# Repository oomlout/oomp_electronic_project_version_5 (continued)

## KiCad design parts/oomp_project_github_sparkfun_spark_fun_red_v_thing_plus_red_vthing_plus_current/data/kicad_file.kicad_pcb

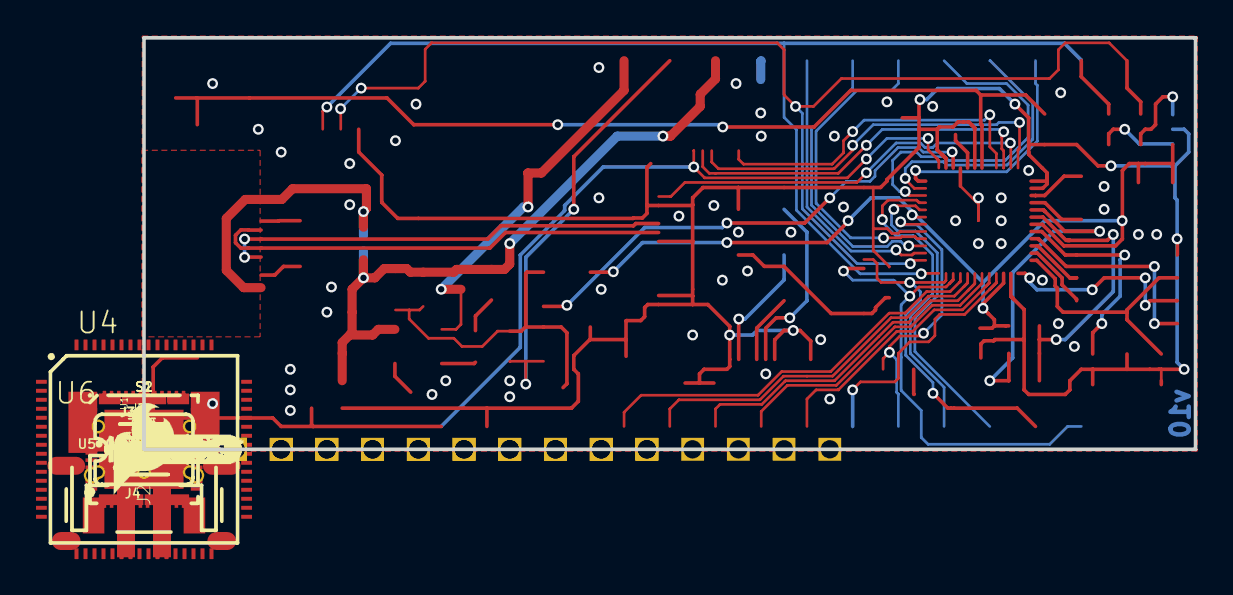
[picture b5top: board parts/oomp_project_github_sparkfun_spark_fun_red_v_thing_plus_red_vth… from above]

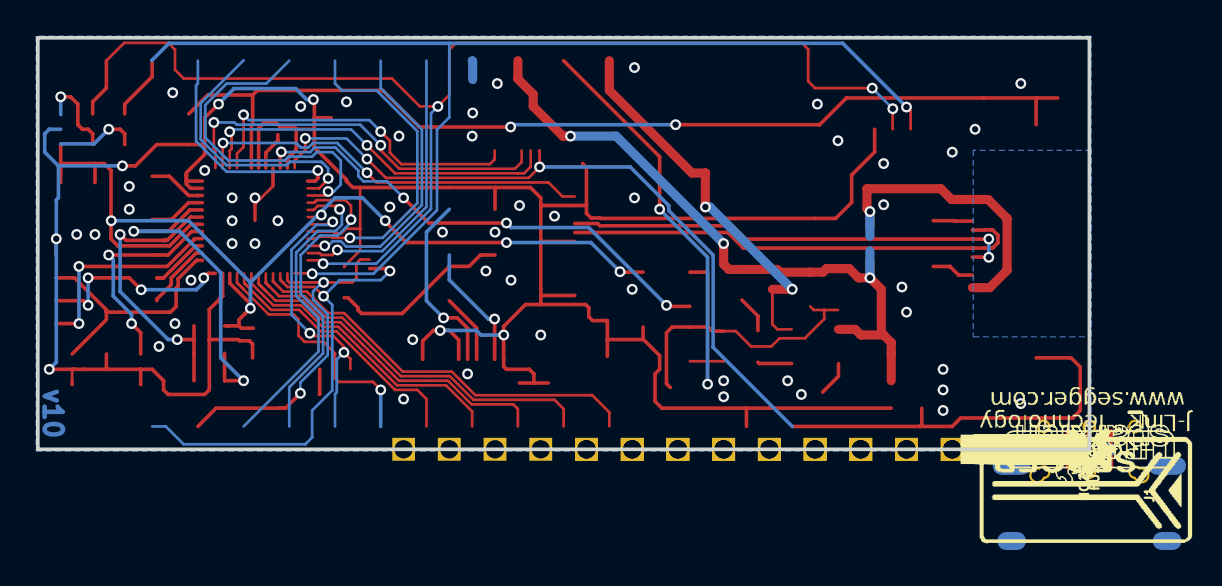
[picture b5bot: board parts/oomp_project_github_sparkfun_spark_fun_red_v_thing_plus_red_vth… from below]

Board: 2 copper layers, 58.4 x 22.9 mm, 137 parts (40 on the bottom side), 60 nets.

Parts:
C1, C3, C30: 10uF; 0603
C2, C10, C12, C17, C18, C23, C24, C25, C26, C27, C28, C29: 0.1uF; 0603
C4, C9, C16: 1.0uF; 0603
C5: 4.7uF; 0603
C6: 47uF/6.3V; 0805
C7: 470nF; 0603
C15: 10uF; EIA3216
D1: 1A/23V/620mV; SOD-323
D2, D4: 24V; 0603
D3: Yellow; LED-0603
F1: 6V 0.5A; 0805
FRAME1, FRAME2: FRAME-LETTER; CREATIVE_COMMONS
FUSE0: JUMPER-SMT_2_NO_NO-SILK; SMT-JUMPER_2_NO_NO-SILK
I2C0: JUMPER-SMT_3_NO_NO-SILK; SMT-JUMPER_3_NO_NO-SILK
J1: FEMALE 2x3; 2X3_TEST_POINTS
J2: USB Female Type C Connector; USB-C-16P
J3: JST-2-SMD
J4: QWIIC_RIGHT_ANGLE; JST04_1MM_RA
J6: 1X12_SM_SQ_NOSILK
J7: 1X16_SM_SQ_NOSILK
JP8, JP9, JP15, JP16: FIDUCIAL1X2; FIDUCIAL-1X2
LED1: BLUE; LED-0603
LOGO2: SFE_LOGO_FLAME.2_INCH; SFE_LOGO_FLAME_.2
NC/GND0: JUMPER-SMT_2_NO_NO-SILK; SMT-JUMPER_2_NO_NO-SILK
Q1: 3.1A/30V/105mΩ; SOT23-3
R1, R9, R10: 4.7k; 0603
R3, R4, R5, R6, R7, R20: 100k; 0603
R8: 100; 0603
R11: 10k; 0603
R12: 2.0k; 0603
R13: 1k; 0603
R18, R19: 5.1k; 0603
S1, S2: MOMENTARY-SWITCH-SPST-SMD-4.6X2.8MM; TACTILE_SWITCH_SMD_4.6X2.8MM
U1: MCP73831; SOT23-5
U2: AP2127K-1.8V; SOT23-5
U3: AP2112-3.3V; SOT23-5
U4: MK22FN128VLH10; LQFP-64
U5: 32MBit; SO08
U6: FE310; QFN-48-.4MMPITCH
U$1: (QWIIC)
U$2: 96
U$3: 26
U$4: 15
U$5: 04
U$6: SDA9
U$8: TXO1
U$9: 107
U$11: 118
U$12: 1811
U$13: RED#V_THING_PLUS_BOARD_SILK#02#JPG
U$14: 1912
U$15: 2013
U$16: OSHW-LOGOS; OSHW-LOGO-S
U$17: 2114
U$18: 2215
U$19: 2316
U$20: EN18
U$21, U$28: GND0
U$22, U$27: NC17
U$23: RXI2
U$24: SCK5
U$25: SCL10
U$26: VBAT19
U$29: #RESET34
U$30: 3V332
U$31: 3V333
U$32: 015
U$33: 114
U$34: 213
U$35: 912
U$36: 1011
U$37: 1110
U$38: CHG0
U$39: 1828
U$40: 1927
U$41: 2026
U$42: RED#V_THING_PLUS_BOARD_SILK#01#JPG
U$43: 2125
U$44: 2224
U$45: SEGGERLOGO#PNG
U$46: 50
U$47: 2323
U$48: EN8
U$49: ASDFKJGHB#JPG
U$50: I2C_______0
U$51, U$67: GND29
U$52: MISO#421
U$53: MOSI#320
U$54: NC#GND31
U$55: NC30
U$56: RST2
U$57: RXI#1619
U$58: SCK#522
U$59: SCL#1316
U$60: SDA#1217
U$61: SI0
U$62: SO1
U$63: TXO#1718
U$64: VBAT7
U$65: VUSB3
U$66: VUSB9
U$68: RESET1
U$69: WAKE0
Y1: 32.768KHZ; CRYSTAL-SMD-2X1.2MM
Y2: 16MHz; RESONATOR-SMD-3.2X1.3

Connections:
1.8V: C1.1, C9.1, C23.1, C24.1, R8.1, U2.5, U6.6, U6.30, U6.46
3.3V: C2.1, C3.1, C6.1, C7.1, C16.1, C17.1, C18.1, C27.1, C28.1, C29.1, C30.1, I2C0.2, J1.2, J4.2, J7.15, R3.2, R5.2, R6.2, R7.2, R20.2, U3.5, U4.3, U4.7, U4.13, U4.14, U4.21, U4.26, U4.30, U4.48, U5.8, U6.11, U6.12, U6.19, U6.23, U6.32, U6.47, Y1.4
5V: C4.1, D1.C, Q1.2, R4.1, U2.1, U3.1
CORE_ENABLE: U2.3, U6.22
D+: J2.A6, J2.B6, U4.5
D-: J2.A7, J2.B7, U4.6
DBG_RESET: J1.4, R20.1, U4.34
DBG_SWDCLK: J1.3, U4.22
DBG_SWDIO: J1.1, U4.25
DBG_SWO: J1.5, U4.24
EN: J6.11, R4.2, U3.3
GND: C1.2, C2.2, C3.2, C4.2, C5.2, C6.2, C7.2, C9.2, C10.2, C12.2, C15.-, C16.2, C17.2, C18.2, C23.2, C24.2, C27.2, C28.2, C29.2, C30.2, D2.1, D4.1, J1.6, J2.GND, J2.GND2, J3.1, J4.1, J7.1, J7.13, LED1.C, NC/GND0.1, R11.1, R12.1, R18.1, R19.1, S1.3, S1.4, S2.3, S2.4, U1.2, U2.2, U3.2, U4.4, U4.15, U4.16, U4.31, U4.47, U5.4, U6.21, U6.49, Y1.2, Y2.2
IO0: J6.3, U6.25
IO1: J6.4, U6.26
IO2: J6.5, U6.27
IO9: J6.6, U6.33
IO10: J6.7, U6.34
IO11: J6.8, U6.35
IO18: J7.12, U6.40
IO19: J7.11, U6.41
IO20: J7.10, U6.42
IO21: J7.9, U6.43
IO22: J7.8, U6.44
IO23: J7.7, U6.45
unnamed: LED1.A, R1.2
unnamed: U6.10, Y2.1
unnamed: J6.9, NC/GND0.2
unnamed: I2C0.1, R9.2
unnamed: I2C0.3, R10.2
unnamed: U6.9, Y2.3
unnamed: U6.20, Y1.3
unnamed: R12.2, U1.5
unnamed: C25.2, C26.2, U6.8
unnamed: D3.C, U1.1
unnamed: J2.B5, R18.2
unnamed: D3.A, R13.2
unnamed: J2.A5, R19.2
PLL_AVDD: C25.1, C26.1, R8.2, U6.7
QSPI_0: U5.5, U6.4
QSPI_1: U5.2, U6.3
QSPI_2: U5.3, U6.2
QSPI_3: R5.1, U5.7, U6.1
QSPI_CS: R3.1, U5.1, U6.5
QSPI_SCK: U5.6, U6.48
RXI: J7.3, U4.40, U6.38
SCL: J4.4, J6.2, R9.1, U6.37
SDA: J4.3, J6.1, R10.1, U6.36
SPI_MISO: J7.4, U6.29
SPI_MOSI: J7.5, U6.28
SPI_SCK: J7.6, R1.1, U6.31
TCK: U4.62, U6.13
TDI: U4.59, U6.16
TDO: U4.2, U6.14
TMS: U4.63, U6.15
TXO: J7.2, U4.39, U6.39
VUSB: C10.1, F1.1, FUSE0.1, J2.VBUS1, J2.VBUS2
V_BATT: J3.2, J6.12, Q1.3, U1.3
V_USB: C5.1, C12.1, C15.+, D1.A, F1.2, FUSE0.2, J6.10, Q1.1, R11.2, R13.1, U1.4
~RESET: D4.2, J7.16, R6.1, S2.1, S2.2, U4.64, U6.24
~WAKE: D2.2, R7.1, S1.1, S1.2, U6.18

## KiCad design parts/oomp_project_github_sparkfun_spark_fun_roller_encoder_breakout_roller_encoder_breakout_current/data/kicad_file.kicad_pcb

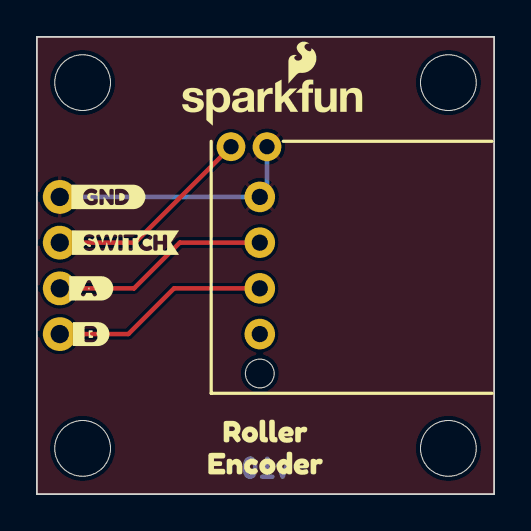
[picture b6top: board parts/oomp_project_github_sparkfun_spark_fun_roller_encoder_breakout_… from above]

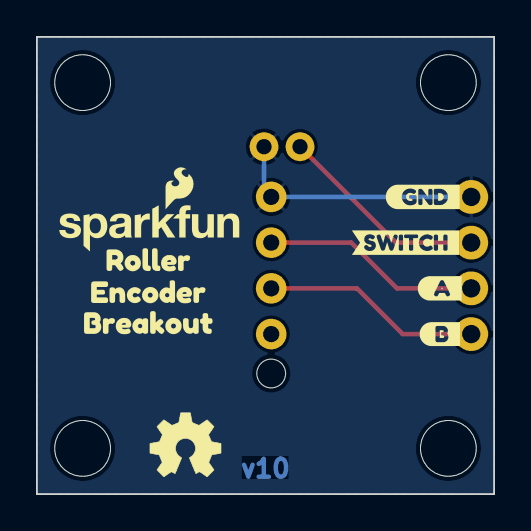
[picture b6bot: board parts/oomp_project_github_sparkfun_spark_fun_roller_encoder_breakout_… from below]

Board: 2 copper layers, 25.4 x 25.4 mm, 21 parts (8 on the bottom side), 4 nets.

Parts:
G1: OSHW_Logo; Creative_Commons_License
J1: Conn_01x04; 1x04
Ref**: Val**; OSHW_Logo_4mm
ST1, ST2, ST3, ST4: Standoff
SW1: Roller_Encoder_Switch; RollerEncoder
kibuzzard-67946CBF: G***; kibuzzard-67946CBF
kibuzzard-67946CF5: G***; kibuzzard-67946CF5
kibuzzard-67946D1E: G***; kibuzzard-67946D1E
kibuzzard-67946D7C: G***; kibuzzard-67946D7C
kibuzzard-67946D9A: G***; kibuzzard-67946D9A
kibuzzard-67946D71: G***; kibuzzard-67946D71
kibuzzard-67946DB3: G***; kibuzzard-67946DB3
kibuzzard-679465CE, kibuzzard-679465CE#2: G***; kibuzzard-679465CE
kibuzzard-679465D4, kibuzzard-679465D4#2: G***; kibuzzard-679465D4
kibuzzard-6794660B: G***; kibuzzard-6794660B
kibuzzard-6794662B: G***; kibuzzard-6794662B

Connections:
A: J1.2, SW1.A
B: J1.1, SW1.B
GND: J1.4, SW1.C, SW1.S2
SWITCH: J1.3, SW1.S1

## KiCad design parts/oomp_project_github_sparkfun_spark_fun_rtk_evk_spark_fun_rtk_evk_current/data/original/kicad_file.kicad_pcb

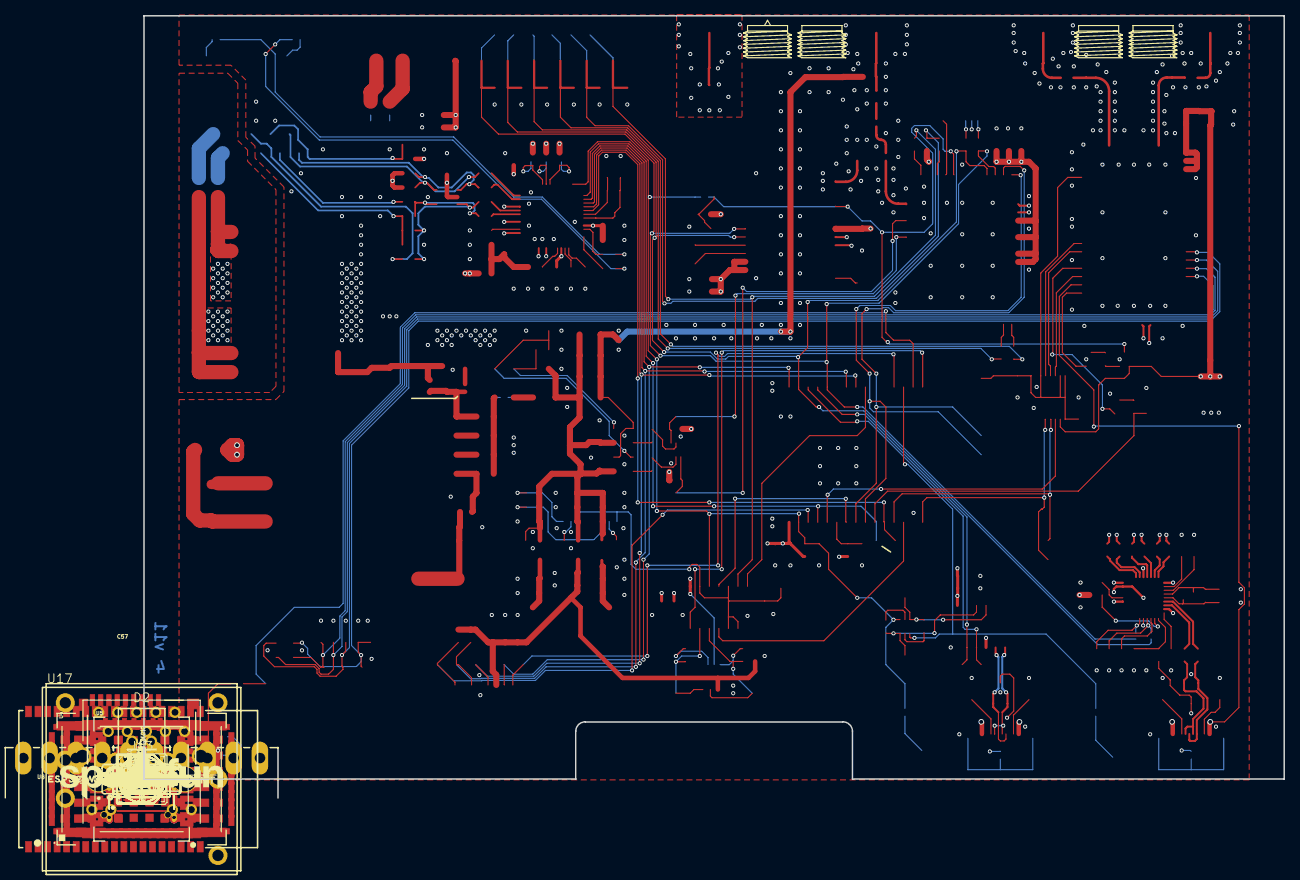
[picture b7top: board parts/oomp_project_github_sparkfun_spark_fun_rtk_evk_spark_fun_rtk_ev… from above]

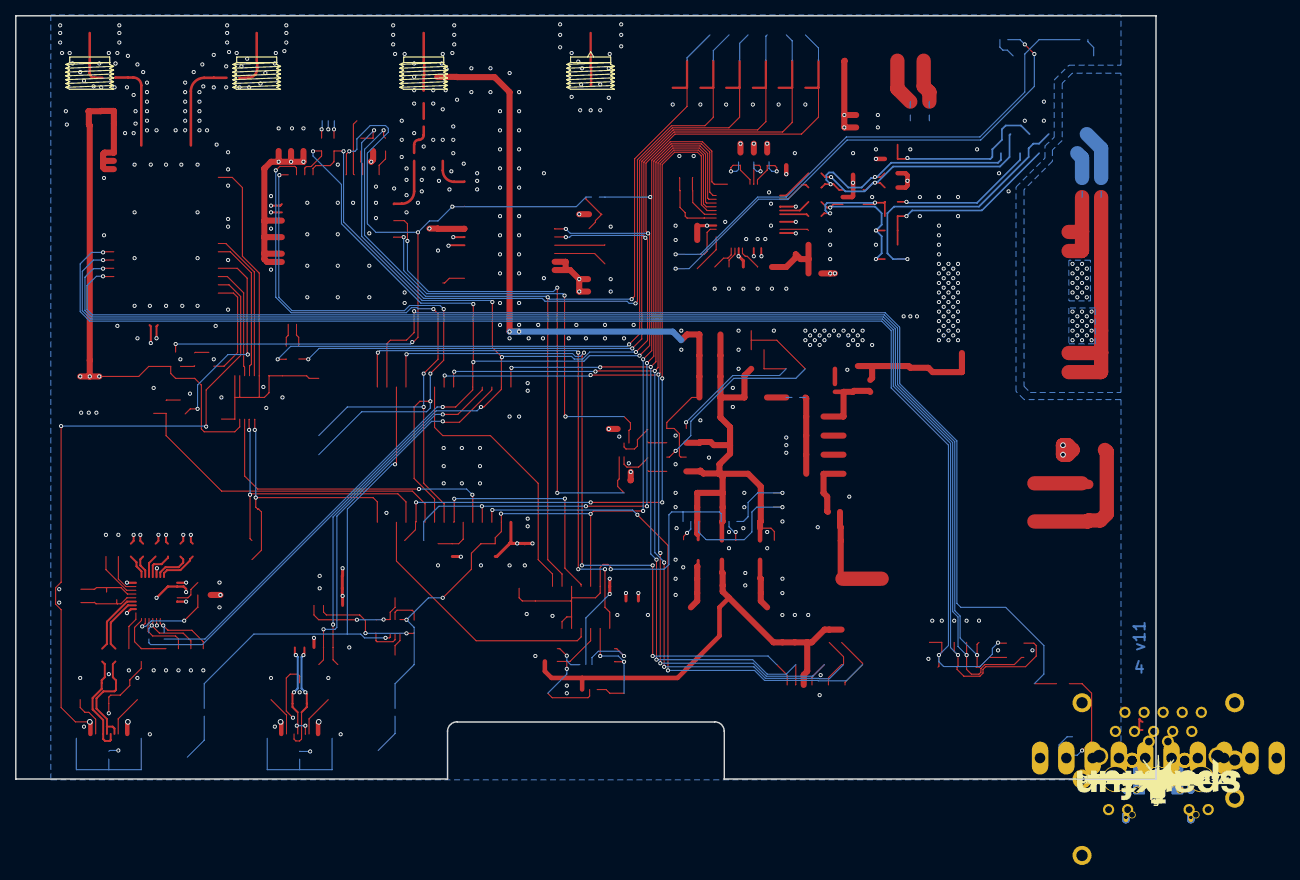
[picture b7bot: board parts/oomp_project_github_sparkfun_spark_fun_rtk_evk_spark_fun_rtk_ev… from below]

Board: 4 copper layers, 151.8 x 101.6 mm, 435 parts (97 on the bottom side), 176 nets.

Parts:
!SAFEBOOT_NEO!0: TEST-POINTPOGO_PTH; 1X01_NO_SILK
!SAFEBOOT_ZED!0: TEST-POINTPOGO_PTH; 1X01_NO_SILK
ACT0: JUMPER-SMT_2_NC_TRACE_SILK; SMT-JUMPER_2_NC_TRACE_SILK
ANT_DET0: TEST-POINTPOGO_PTH; 1X01_NO_SILK
ANT_SHT0: TEST-POINTPOGO_PTH; 1X01_NO_SILK
BOOT0: MOMENTARY-SWITCH-SPST-PTH-RIGHT-ANGLE-8-020; TACTILE_SWITCH_PTH_RA_8-020
BOOT_SW0: JUMPER-SMT_2_NC_TRACE_SILK; SMT-JUMPER_2_NC_TRACE_SILK
BYPASS1, BYPASS2: NO PASTE; SMT-JUMPER_2_SOIC-PAD_NO-PASTE
C1, C3, C5, C6, C8, C9, C10, C14, C18, C22, C23, C25, C26, C29, C56, C59, C60: 2.2uF; 0603
C2, C7, C15, C17, C19, C21, C30, C31, C33, C34, C35, C36, C37, C38, C52, C53, C54, C58, C61, C62, C65, C66, C67, C68, C69, C70, C75, C78: 0.1uF; 0603
C4, C40, C43: 10nF; 0603
C11, C13, C71, C72, C73, C74: 47pF; 0603
C12, C24: 1.0uF; 0603
C16, C48, C57, C76: 100uF; PANASONIC_D
C20, C32, C39, C55: 10uF; 0603
C27, C28: 10pF; 0603
C41: 4.7uF; 0603
C42: 1nF; 1206
C44, C45: 6.8nF; 0603
C46: 22nF; 0603
C47, C49, C50, C51, C77, C84, C85: 10uF; 0805
C63, C64: 18pF; 0603
C79: 15pF; 0603
C80: 8.2pF; 0603
C81: 68pF; 0603
C82, C83: 33pF; 0603
C86: 47UF; PANASONIC_D
D1, D12, D13, D15, D16, D17, D18, D19, D20: PESD0402-0402; 0402
D2: LED-RIGHT-ANGLE-PTH-GREEN; CBI-RIGHT-ANGLE-PTH
D3: PESD0402; 0402
D4, D5, D6, D9: 3A/10V/280mV; SOD-323
D7, D8, D10: ESD Diode; SOT-23-6
D11: TVS_DIODE; SOT23-6L
D14: 3A/40V; SMA-DIODE
DET0: TEST-POINTPOGO_PTH; 1X01_NO_SILK
DTR0: TEST-POINTPOGO_PTH; 1X01_NO_SILK
ESP32_RF0: ANTENNA-SMA-GROUNDEDEDGE_RPSMA; RP-SMA-EDGE
ETH_CS0: TEST-POINTPOGO_PTH; 1X01_NO_SILK
ETH_INT0: TEST-POINTPOGO_PTH; 1X01_NO_SILK
F1: 6V/2A; 1210
FB1: 600Ω; 0805
FB2: 470Ω; 0603
FD1, FD2, FD3, FD4: FIDUCIAL1X2; FIDUCIAL-1X2
FRAME1: FRAME-LEDGER; CREATIVE_COMMONS
FRAME2: FRAME-LEDGERNO_FOOTPRINT; DUMMY
GND0: TEST-POINTPOGO_PTH; 1X01_NO_SILK
GNSS_RESET0: JUMPER-COMBO_2_NO; COMBO-JUMPER_2_NO
GNSS_RF0: ANTENNA-SMA-GROUNDEDEDGE_SMA; SMA-EDGE
H1, H2, H3, H4, H5, H6: STAND-OFFTIGHT; STAND-OFF-TIGHT
I2C0, I2C1: JUMPER-SMT_3_NO_SILK; SMT-JUMPER_3_NO_SILK
J1, J6: USB-C-16P_4LAYER-PADS
J2: NANO_SIM_PP
J3: MICRO-SD-PUSH-PUSH-EXT-PIN; MICROSD-EXTERNALPIN
J4: Vertical Qwiic Connector; JST04_1MM_VERT
J8: U.FL_REDUCED_FOOTPRINT
J9: MAGJACK-POE; MAGJACK-SYM_LED
J13: 1X10_SCREW_TERMINAL_3.5MM
L1, L4: 2.2uH; 0805-WIDE
L2, L3: DNP; 0603_NO-CREAM
LARA_RF1, LARA_RF2: ANTENNA-SMA-GROUNDEDEDGE_SMA; SMA-EDGE
LED0: JUMPER-SMT_2_NC_TRACE_SILK; SMT-JUMPER_2_NC_TRACE_SILK
LINK0: JUMPER-SMT_2_NC_TRACE_SILK; SMT-JUMPER_2_NC_TRACE_SILK
LOAD0: JUMPER-SMT_2_NC_TRACE_SILK; SMT-JUMPER_2_NC_TRACE_SILK
LOGO1: SPECIAL_INSTRUCTIONS-ORDERING; ORDERING_INSTRUCTIONS
LOGO2: QWIIC_LOGO_6MM; QWIIC_6MM
LOGO4: OSHW-LOGOS; OSHW-LOGO-S
LOGO5, LOGO7: SFE_LOGO_NAME.2_INCH; SFE_LOGO_NAME_.2
LOGO6, LOGO8: SFE_LOGO_FLAME.2_INCH; SFE_LOGO_FLAME_.2
MEAS0: JUMPER-COMBO_2_NC_TRACE; COMBO-JUMPER_2_NC_TRACE
NEO_RX0: TEST-POINTPOGO_PTH; 1X01_NO_SILK
NEO_TX0: TEST-POINTPOGO_PTH; 1X01_NO_SILK
PICO0: TEST-POINTPOGO_PTH; 1X01_NO_SILK
PM0, PM1, PM2: JUMPER-SMT_2_NO_SILK; SMT-JUMPER_2_NO_SILK
POCI0: TEST-POINTPOGO_PTH; 1X01_NO_SILK
PW+0: JUMPER-COMBO_2_NC_TRACE; COMBO-JUMPER_2_NC_TRACE
PW-0: JUMPER-COMBO_2_NC_TRACE; COMBO-JUMPER_2_NC_TRACE
PWREN0: TEST-POINTPOGO_PTH; 1X01_NO_SILK
Q1, Q2: SC70-6
Q5, Q6: 310mA/60V/1.6Ω; SOT323
R1, R2, R33, R34: 5.1k; 0603
R3, R4, R5, R11, R15, R28, R30, R31, R32, R49, R54, R57, R58, R64: 10k; 0603
R6, R27, R36, R37, R38, R39, R46, R47: 33; 0603
R7, R8, R9, R10, R22, R23, R66, R67: 27; 0603
R12: 12k; 0603
R13, R24: 1M; 0603
R14, R17, R18, R20, R21, R44, R48, R50, R51, R52, R65, R69: 100k; 0603
R16, R19, R71, R72: 2.2k; 0603
R25, R26, R53, R56, R63, R68, R70: 1k; 0603
R29: 12.4k; 0603
R35, R40, R41, R42: 49.9; 0603
R43: 10; 0603
R45, R55, R59, R60, R61: 49.9 1/2W; 1206
R62: 470; 0603
RESET0: MOMENTARY-SWITCH-SPST-PTH-RIGHT-ANGLE-8-020; TACTILE_SWITCH_PTH_RA_8-020
RESET_SW0: JUMPER-SMT_2_NC_TRACE_SILK; SMT-JUMPER_2_NC_TRACE_SILK
RTS0: TEST-POINTPOGO_PTH; 1X01_NO_SILK
RX0, RX2: TEST-POINTPOGO_PTH; 1X01_NO_SILK
RXD0: TEST-POINTPOGO_PTH; 1X01_NO_SILK
SCK0: TEST-POINTPOGO_PTH; 1X01_NO_SILK
SCL0, SCL2: TEST-POINTPOGO_PTH; 1X01_NO_SILK
SDA0, SDA2: TEST-POINTPOGO_PTH; 1X01_NO_SILK
SD_CS0: TEST-POINTPOGO_PTH; 1X01_NO_SILK
SHLD1, SHLD2: JUMPER-SMT_2_NC_TRACE_SILK; SMT-JUMPER_2_NC_TRACE_SILK
SPWR0: JUMPER-SMT_3_1-NC_TRACE_SILK; SMT-JUMPER_3_1-NC_TRACE_SILK
TP0: TEST-POINTPOGO_PTH; 1X01_NO_SILK
TPWR0: JUMPER-SMT_3_1-NC_TRACE_SILK; SMT-JUMPER_3_1-NC_TRACE_SILK
TP_BOOT0: TEST-POINTPOGO_PTH; 1X01_NO_SILK
TP_LED0: TEST-POINTPOGO_PTH; 1X01_NO_SILK
TX0, TX2: TEST-POINTPOGO_PTH; 1X01_NO_SILK
TXD0: TEST-POINTPOGO_PTH; 1X01_NO_SILK
U1: ESP32-WROVER-IE; ESP32-WROVER-E_IE
U2: CH340C; SO016
U3, U6: XC6222B331MR-G; SOT23-5
U4: U-BLOX_ZED-F9P; ZED-F9P
U5: U-BLOX_NEO-D9S-00B; NEO-M9N_M8T_M8U_D9S
U7: W5500; LQFP-48
U8: LARA-R6001D; LARA-LGA
U9: 74LVC4066D_QUAD_BILATERAL_SWITCH; SO14
U10: POE_PSU-DP990X; DP990X
U11, U13: MCP6021T; SOT23-5
U12: AP7361C-33; UDFN-8
U14: BP2G1+_POWER_SPLITTER; XX21
U15: USB251XB_USB2514B; QFN-36
U16: SN74AVC4T774PW; SOP65P640X120-16N
U17: URB2405YMD; URB_YMD-15WR3
U18: 74HC1G04; SOT353
U$2: 33_#_ZED_RXI0
U$3, U$45: #SHLD#0
U$4, U$46, U$48: #I�C#0
U$5, U$113: PW#0
U$6, U$114: PW#1
U$7, U$149: 0_#_BOOT0
U$8, U$12, U$41, U$93: #SAFEBOOT#2226
U$9: #ACT#0
U$10: #LINK#1
U$11, U$13: RTK_EVK0
U$14: NEO_TX2
U$15: NEO_RX3
U$16, U$18: GND2
U$17, U$65: 3V3_SW20
U$19: 12_#_SDA20
U$20: 15_#_SCL213
U$21: ESP32_WIFI_#_BT0
U$22, U$23: 3V3_SW3
U$24, U$107: VCCA0
U$25, U$26: 21_#_SDA4
U$28, U$30: 22_#_SCL22
U$29, U$111: 27_#_#ETH_CS#0
U$31, U$32: ZED_RX223
U$33, U$36: ZED_TX2224
U$34, U$99: 1_#_TX20
U$35, U$100: 3_#_RX20
U$37, U$38: ZED_EXTINT2225
U$39, U$40: ZED_TP2226
U$42, U$94: ANT_DET2227
U$43, U$95: #ANT_SHT#2228
U$44, U$106: 9#2230
U$47, U$104: 99#2230
U$49, U$105: V_ANT2229
U$55, U$76: RTS2231
U$56, U$77: DTR2232
U$57, U$66: 2_#_LED0
U$58: #LED#2234
U$59, U$88: 3V3_SW25
U$60, U$87: 3V325
U$61, U$86: 5V25
U$62, U$84: MEAS2
U$63, U$70: VIN#0
U$64: 36_#_SD_DET0
U$67: #PMODE0#0
U$68: #PMODE1#1
U$69: #PMODE2#2
U$71, U$72: VIN#1
U$73, U$108: 14_#_RXDO0
U$74: #RESET#0
U$75, U$103: 13_#_TXDI15
U$78: ESP320
U$79, U$110: 39_#_#ETH_INT#0
U$80, U$141: PWR_EN2233
U$81: V_POE0
U$82: V_USB3
U$83: V_USB24
U$85: VIN1
U$89: 4_#_#SD_CS#15
U$90: 25_#_ZED_TXO0
U$91, U$92: NO0
U$96: CELLULAR2
U$97: L#BAND1
U$98: 23_#_PICO23
U$101: 19_#_POCI19
U$102: 18_#_SCK6
U$115, U$116: VCCIO0
U$117: #3V3_SW_EN#0
U$118: #3V3_SW2_EN#0
U$135, U$143: GND12
U$136: POE_LOAD0
U$146, U$147: HIGH_TEMP_WARNING
U$148: RESET0
U$152, U$153: RTK5#SVG0
U$154: #GNSS_RESET#0
UNK3V3, UNK3V3_SW0, UNK3V3_SW2, UNK5V0, UNK9%0, UNK99%0: TEST-POINTPOGO_PTH; 1X01_NO_SILK
USB251SCL0, USB251SDA0: SMT-JUMPER_2_NO_SILK
VANT0: TEST-POINTPOGO_PTH; 1X01_NO_SILK
VCCA0: TEST-POINTPOGO_PTH; 1X01_NO_SILK
VCCIO0: TEST-POINTPOGO_PTH; 1X01_NO_SILK
VID1: 10k; 0603
VID2: 1k; 0603
VIN0: TEST-POINTPOGO_PTH; 1X01_NO_SILK
VIN+0: JUMPER-COMBO_2_NC_TRACE; COMBO-JUMPER_2_NC_TRACE
VIN-0: JUMPER-COMBO_2_NC_TRACE; COMBO-JUMPER_2_NC_TRACE
VPOE0: TEST-POINTPOGO_PTH; 1X01_NO_SILK
VUSB0, VUSB2: TEST-POINTPOGO_PTH; 1X01_NO_SILK
Y1: 25MHz; CRYSTAL-SMD-2.0X1.6MM
Y2: 24MHz; CRYSTAL-SMD-2.0X1.6MM
ZED_EXTINT0: TEST-POINTPOGO_PTH; 1X01_NO_SILK
ZED_RXI0: TEST-POINTPOGO_PTH; 1X01_NO_SILK
ZED_TXO0: TEST-POINTPOGO_PTH; 1X01_NO_SILK

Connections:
3.3V: C1.1, C2.1, C3.1, C4.1, C14.1, C15.1, C25.1, C26.1, I2C0.2, R3.2, U1.2, U2.4, U2.16, U6.5, U9.14, UNK3V3.1, VID2.1
3.3V_SW: C5.1, C6.1, C7.1, C12.1, C18.1, C19.1, C20.1, C21.1, C24.1, C29.1, C30.1, C32.1, C52.1, C55.1, C56.1, C62.1, FB2.1, I2C1.2, J3.4, J4.2, J9.11, J9.13, J13.7, R11.2, R18.2, R28.2, R30.2, R31.2, R32.2, R54.1, R57.1, R64.2, R65.2, U3.5, U4.33, U4.34, U4.36, U4.38, U5.7, U5.22, U5.23, U7.28, U15.5, U15.10, U15.15, U15.23, U15.29, U15.36, UNK3V3_SW0.1
3.3V_SW2: C60.1, C61.1, C76.+, C77.1, C78.1, C79.1, C80.1, C81.1, U8.51, U8.52, U8.53, U12.1, U16.15, U18.5, UNK3V3_SW2.1
5V: C8.1, C9.1, C10.1, C17.1, C22.1, C23.1, C53.1, C54.1, C57.+, C59.1, F1.1, R50.2, R51.2, R53.1, R55.1, R59.1, R60.1, R61.1, U3.1, U6.1, U6.3, U11.5, U12.8, U13.5, UNK5V0.1
5V_RAW: C48.+, C49.1, C50.1, L1.1, U10.1, U10.2
5V_RAW1: C16.+, C51.1, C84.1, L4.1, U17.4
9%: R48.2, R58.1, U13.3, UNK9%0.1
99%: R48.1, R53.2, U11.4, UNK99%0.1
ACT: ACT0.1, J9.14
ACT_LED: R26.2, U7.27
ANT: C13.2, U14.2
ANT_DET: ANT_DET0.1, Q2.3, R54.2, U4.4
ANT_NEO: U5.11, U14.5
ANT_ZED: U4.2, U14.8
BYPASS: BYPASS1.1, BYPASS2.1
CH340-DTR: DTR0.1, Q1.1, R4.2, U2.13
CH340-RTS: Q1.4, R5.2, RTS0.1, U2.14
CH340-RXI: TX0.1, U1.35, U2.3
CH340-TXO: RX0.1, U1.34, U2.2
D+: D10.1, J1.A6, J1.B6, U2.5
D+_LARA: R10.1, U15.2
D+_NEO: R66.1, U15.7
D+_UBLOX: D8.1, J6.A6, J6.B6, R23.1
D+_ZED: R7.1, U15.4
D-: D10.3, J1.A7, J1.B7, U2.6
D-_LARA: R9.1, U15.1
D-_NEO: R67.1, U15.6
D-_UBLOX: D8.3, J6.A7, J6.B7, R22.1
D-_ZED: R8.1, U15.3
ESP0/~BOOT: BOOT_SW0.1, Q1.6, TP_BOOT0.1, U1.25
ESP2/LED: R62.1, TP_LED0.1, U1.24
ESP4/~SD_CS: J3.2, SD_CS0.1, U1.26
ESP5/TP: U1.29, U9.8
ESP12/SDA2: U1.14, U9.4
ESP13/LARA_TXDI: TXD0.1, U1.16, U16.12
ESP14/LARA_RXDO: RXD0.1, U1.13, U16.13
ESP15/SCL2: U1.23, U9.1
ESP18/SCK: J3.5, SCK0.1, U1.30, U7.33
ESP19/POCI: J3.7, POCI0.1, R11.1, U1.31, U7.34
ESP21/SDA: D15.1, J13.6, R72.1, SDA0.1, U1.33, U4.44, U5.18, USB251SDA0.1
ESP22/SCL: D16.1, J13.5, R71.1, SCL0.1, U1.36, U4.45, U5.19, USB251SCL0.1
ESP23/PICO: J3.3, PICO0.1, U1.37, U7.35
ESP25/ZED_TXO: U1.10, U4.42, ZED_TXO0.1
ESP26/LARA_PWR_ON: R69.2, R70.1, U1.11
ESP27/~ETH_CS: ETH_CS0.1, U1.12, U7.32
ESP32/PWREN: U1.8, U9.11
ESP33/ZED_RXI: U1.9, U4.43, ZED_RXI0.1
ESP34/LARA_NI: U1.6, U16.14
ESP35/VID: U1.7, VID1.2, VID2.2
ESP36/SD_DET: DET0.1, J3.9, R65.1, U1.4
ESP39/~ETH_INT: ETH_INT0.1, U1.5, U7.36
GND: BOOT0.1, C1.2, C2.2, C3.2, C4.2, C5.2, C6.2, C7.2, C8.2, C9.2, C10.2, C11.2, C12.2, C14.2, C15.2, C16.-, C17.2, C18.2, C19.2, C20.2, C21.2, C22.2, C23.2, C24.2, C25.2, C26.2, C27.2, C28.2, C29.2, C30.2, C31.2, C32.2, C33.2, C34.2, C35.2, C36.2, C37.2, C38.2, C39.2, C40.2, C41.2, C42.2, C43.2, C46.2, C47.2, C48.-, C49.2, C50.2, C51.2, C52.2, C53.2, C54.2, C55.2, C56.2, C57.-, C58.2, C59.2, C60.2, C61.2, C62.2, C63.1, C64.1, C65.2, C66.2, C67.2, C68.2, C69.2, C70.2, C71.2, C72.1, C73.2, C74.1, C75.1, C76.-, C77.2, C78.2, C79.2, C80.2, C81.2, C84.2, C85.2, D1.2, D2.C, D3.2, D7.2, D8.2, D10.2, D11.2, D11.5, D12.2, D13.2, D15.2, D16.2, D17.2, D18.2, D19.2, D20.2, ESP32_RF0.GND@0, ESP32_RF0.GND@1, ESP32_RF0.GND@2, ESP32_RF0.GND@3, GND0.1, GNSS_RF0.GND@0, GNSS_RF0.GND@1, GNSS_RF0.GND@2, GNSS_RF0.GND@3, J1.GND, J1.GND2, J2.C5, J3.6, J3.10, J3.11, J3.12, J3.13, J4.1, J6.GND, J6.GND2, J8.1, J8.2, J13.8, L2.2, L3.2, LARA_RF1.GND@0, LARA_RF1.GND@1, LARA_RF1.GND@2, LARA_RF1.GND@3, LARA_RF2.GND@0, LARA_RF2.GND@1, LARA_RF2.GND@2, LARA_RF2.GND@3, PM0.1, PM1.1, PM2.1, Q2.1, Q2.4, Q5.2, Q6.2, R1.1, R2.1, R12.2, R14.1, R15.1, R17.1, R20.1, R29.1, R33.1, R34.1, R44.1, R45.1, R49.1, R52.1, R58.2, R69.1, RESET0.1, SHLD1.1, SHLD2.1, U1.1, U1.15, U1.38, U1.GND, U1.GNDT1, U1.GNDT2, U1.GNDT3, U1.GNDT4, U1.GNDT5, U1.GNDT6, U1.GNDT7, U1.GNDT8, U2.1, U3.2, U4.1, U4.3, U4.12, U4.14, U4.32, U4.37, U4.41, U4.48, U4.55, U4.56, U4.57, U4.58, U4.59, U4.60, U4.61, U4.62, U4.63, U4.64, U4.65, U4.66, U4.67, U4.68, U4.69, U4.70, U4.71, U4.72, U4.73, U4.74, U4.75, U4.76, U4.77, U4.78, U4.79, U4.80, U4.81, U4.82, U4.83, U4.84, U4.85, U4.86, U4.87, U4.88, U4.89, U4.90, U4.91, U4.92, U4.93, U4.94, U4.95, U4.96, U4.97, U4.98, U4.99, U4.100, U4.101, U4.102, U5.10, U5.12, U5.13, U5.24, U6.2, U7.3, U7.9, U7.14, U7.16, U7.19, U7.29, U7.48, U8.1, U8.3, U8.5, U8.9, U8.10, U8.14, U8.20, U8.21, U8.22, U8.30, U8.32, U8.43, U8.50, U8.54, U8.55, U8.57, U8.58, U8.60, U8.61, U8.63, U8.64, U8.65, U8.66, U8.67, U8.68, U8.69, U8.70, U8.71, U8.72, U8.73, U8.74, U8.75, U8.76, U8.77, U8.78, U8.79, U8.80, U8.81, U8.82, U8.83, U8.84, U8.85, U8.86, U8.87, U8.88, U8.89, U8.90, U8.91, U8.92, U8.93, U8.94, U8.95, U8.96, U9.7, U10.3, U11.2, U12.4, U12.EP, U13.2, U14.1, U14.3, U14.4, U14.6, U14.7, U15.11, U15.EP, U16.7, U16.9, U16.10, U17.6, U18.3, VID1.1
GND-ISO: C42.1, J9.7, J9.8, J9.S1, J9.S2
GNSS_~RESET: C58.1, GNSS_RESET0.1, GNSS_RESET0.3, R64.1, U4.49, U5.8, U18.2
LARA_18_NI: U8.16, U16.3
LARA_18_RXDO: U8.13, U16.4
LARA_18_TXDI: U8.12, U16.5
LARA_PWR_ON: Q5.3, U8.15
LARA_~RESET: Q6.3, U8.18
LINK: J9.12, LINK0.1
LINK_LED: R25.2, U7.25
MEAS: D4.C, D5.C, D6.C, D9.C, MEAS0.2, MEAS0.4
unnamed: J1.B5, R1.2
unnamed: J1.A5, R2.2
unnamed: R7.2, U4.40
unnamed: Q1.2, R5.1
unnamed: Q1.5, R4.1
unnamed: R8.2, U4.39
unnamed: LED0.2, R62.2
unnamed: J6.SHLD1, J6.SHLD2, J6.SHLD3, J6.SHLD4, SHLD2.2
unnamed: R27.1, U4.51
unnamed: F1.2, MEAS0.1, MEAS0.3
unnamed: R46.1, U4.27
unnamed: ACT0.2, R26.1
unnamed: D3.1, ESP32_RF0.SIG, J8.FEED
unnamed: I2C0.3, R16.2
unnamed: I2C0.1, R19.2
unnamed: R68.1, U18.4
unnamed: R66.2, U5.6
unnamed: R67.2, U5.5
unnamed: C27.1, R24.1, U7.31, Y1.1
unnamed: C28.1, R24.2, U7.30, Y1.3
unnamed: LINK0.2, R25.1
unnamed: R50.1, SPWR0.3
unnamed: R29.2, U7.10
unnamed: C40.1, U7.22
unnamed: C41.1, U7.20
unnamed: SPWR0.2, U3.3
unnamed: LOAD0.1, R45.2
unnamed: RESET0.2, RESET_SW0.2
unnamed: BOOT0.2, BOOT_SW0.2
unnamed: R49.2, U7.23
unnamed: R51.1, TPWR0.3
unnamed: R47.1, U4.26
unnamed: J6.B5, R33.2
unnamed: J6.A5, R34.2
unnamed: R56.1, U11.1
unnamed: R6.1, U4.53
unnamed: Q2.5, R56.2
unnamed: TPWR0.2, U12.5
unnamed: Q2.2, R63.2
unnamed: R63.1, U13.1
unnamed: Q6.1, R68.2
unnamed: I2C1.3, R71.2
unnamed: I2C1.1, R72.2
unnamed: D2.A, LED0.1
unnamed: R9.2, U8.28
unnamed: R10.2, U8.29
unnamed: C63.2, R13.2, U15.33, Y2.3
unnamed: C64.2, R13.1, U15.32, Y2.1
unnamed: R12.1, U15.35
unnamed: R14.2, U15.28
unnamed: R17.2, U15.25
unnamed: C65.1, U15.34
unnamed: C66.1, U15.14
unnamed: R22.2, U15.30
unnamed: R23.2, U15.31
unnamed: C82.2, D12.1, LARA_RF1.SIG
unnamed: C82.1, L2.1, U8.56
unnamed: C83.2, D13.1, LARA_RF2.SIG
unnamed: C83.1, L3.1, U8.62
unnamed: Q5.1, R70.2
NEO_RXI: NEO_RX0.1, U5.21
NEO_TXO: NEO_TX0.1, U5.20
PMODE0: PM0.2, R30.1, U7.45
PMODE1: PM1.2, R31.1, U7.44
PMODE2: PM2.2, R32.1, U7.43
PW1+: PW+0.1, PW+0.3, U10.5, U10.6
PW1-: PW-0.1, PW-0.3, U10.7, U10.8
PW+: J9.9, PW+0.2, PW+0.4
PW-: J9.10, PW-0.2, PW-0.4
PWREN: PWREN0.1, R15.2, SPWR0.1, TPWR0.1, U9.5, U9.6, U9.10, U9.13
RCT: C43.1, J9.5, R35.1, R40.1
RD+: C45.2, J9.3
RD-: C44.2, J9.6
RF: C13.1, D1.1, FB1.2, GNSS_RF0.SIG
RXN: R39.1, U7.5
RXN1: C44.1, D7.4, R39.2, R40.2
RXP: R38.1, U7.6
RXP1: C45.1, D7.3, R35.2, R38.2
SCL2: J4.4, R16.1, SCL2.1, U9.2
SDA2: J4.3, R19.1, SDA2.1, U9.3
SHIELD: J1.SHLD1, J1.SHLD2, J1.SHLD3, J1.SHLD4, SHLD1.2
SIM_CLK: C71.1, D11.1, J2.C3, U8.38
SIM_IO: C74.2, D11.6, J2.C7, U8.39
SIM_RST: C72.2, D11.4, J2.C2, U8.40
TCT: C46.1, J9.4, R43.1
TD+: D7.6, J9.1, R36.2, R41.1
TD-: D7.1, J9.2, R37.2, R42.1
TXN: R37.1, U7.1
TXP: R36.1, U7.2
USB251SCL: R52.2, U15.24, USB251SCL0.2
USB251SDA: R44.2, U15.22, USB251SDA0.2
USB_~RESET: C67.1, R18.1, U15.26
VBUS_DET: C68.1, R20.2, R21.1, U15.27
VCCA: C33.1, C34.1, C35.1, C36.1, C37.1, C38.1, C39.1, D7.5, FB2.2, R41.2, R42.2, R43.2, U7.4, U7.8, U7.11, U7.15, U7.17, U7.21, VCCA0.1
VCCIO: C69.1, C70.1, U8.4, U16.1, U16.2, U16.6, U16.8, U16.16, VCCIO0.1
VIN: C85.1, D4.A, L4.2, VIN0.1
VIN1+: D14.A, VIN+0.1, VIN+0.3
VIN1-: C86.-, U17.2, VIN-0.2, VIN-0.4
VIN2+: C86.+, D14.C, U17.3
VIN+: J13.10, VIN+0.2, VIN+0.4
VIN-: J13.9, VIN-0.1, VIN-0.3
VSIM: C73.1, C75.2, D11.3, J2.C1, U8.41
V_ANT: C11.1, FB1.1, R55.2, R59.2, R60.2, R61.2, U11.3, U13.4, VANT0.1
V_POE: C47.1, D9.A, L1.2, LOAD0.2, VPOE0.1
V_USB: D5.A, D10.5, J1.VBUS1, J1.VBUS2, VUSB0.1
V_USB_2: D6.A, D8.5, J6.VBUS1, J6.VBUS2, R21.2, U8.17, VUSB2.1
ZED_EXTINT: D19.1, J13.2, R27.2, R28.1, ZED_EXTINT0.1
ZED_RX2: D17.1, J13.4, R47.2, RX2.1
ZED_TP: D20.1, J13.1, R6.2, TP0.1, U9.9
ZED_TX2: D18.1, J13.3, R46.2, TX2.1
~ANT_SHORT: ANT_SHT0.1, Q2.6, R57.2, U4.6
~RESET: C31.1, GNSS_RESET0.2, GNSS_RESET0.4, Q1.3, R3.1, RESET_SW0.1, U1.3, U7.37, U9.12
~SAFEBOOT_NEO: !SAFEBOOT_NEO!0.1, U5.1
~SAFEBOOT_ZED: !SAFEBOOT_ZED!0.1, U4.50
